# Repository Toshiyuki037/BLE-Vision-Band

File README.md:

<!-- BADGES -->

<br />

<!-- TITLE -->

<div align="center">
  <h1>WBLE Vision Band</h1>
  <p><strong>Embedded BLE Vision System with Haptic Feedback</strong></p>

  <p>
    A wrist-mounted system that performs on-device image recognition and communicates results through real-time haptic feedback.
  </p>

  <br />

<a href="#">🎥 View Demo (Coming Soon)</a>

</div>

---

## 📌 Overview

Vision-Band is a wearable embedded system designed to explore on-device perception in resource-constrained environments.

Motivated by the limitations of the Even Realities G2 Frames—specifically the lack of an integrated camera—this project implements a modular vision pipeline paired with a haptic feedback interface for real-time, non-visual interaction.

---

## 🧠 System Architecture

```bash
[Camera] → [nRF5340 MCU] → [Processing / ML] → [DRV2605L] → [Vibration Motor]
                               ↓
                             [BLE]
```

* SPI camera streams image data to MCU
* MCU performs lightweight processing / inference
* Haptic driver converts results into vibration feedback
* BLE enables debugging + external communication

---

## 🔧 Hardware Components

* NRF5340-DK — main MCU + BLE
* Arducam Mega 5MP SPI Camera — image capture
* DRV2605L — haptic driver
* 3V vibration motor — feedback output
* Li-ion battery (500mAh) — power
* TP4056 — charging module

---

## DOCUMENTATION (BOM)

A dated and recorded log of all my research and development.
👉 https://app.notion.com/p/Vision-Band-3348546487d380519d59cf720e47a7b5

---

## 📦 Bill of Materials (BOM)

A detailed breakdown of all components, costs, and sourcing is available below:

👉 https://docs.google.com/spreadsheets/d/1EQedtdF9KUZCxSDgVT32OZnp6HhoeuN5VWY41QO01Ro/edit?usp=sharing

* Includes part numbers, suppliers, and prototyping cost (~$187)
* Documents full hardware stack for reproducibility

---

## ⚙️ Software Stack

* Embedded firmware (C/C++)
* SPI image acquisition pipeline
* I²C haptic control (DRV2605L)
* BLE communication (Nordic SDK)
* Lightweight image recognition (TinyML / rule-based)

---

## 🚀 Features

* On-device image capture and processing
* Real-time haptic feedback output
* BLE-enabled communication interface
* Fully self-contained wearable prototype
* End-to-end embedded system (hardware + firmware integration)

---

## 📊 Challenges & Engineering Tradeoffs

* **Memory constraints:** Limited RAM for image buffering
* **Bandwidth limits:** SPI camera throughput bottlenecks
* **Power system limitations:** TP4056 lacks load sharing
* **Compute vs latency:** Balancing ML accuracy and responsiveness

---

## 🔋 Power Considerations

* Powered by 3.7V Li-ion battery (500mAh)
* Charging via TP4056
* System currently optimized for prototyping, not all-day wearable use

---

## 🛠️ Getting Started

### Prerequisites

* Arduino IDE or Nordic SDK
* USB connection for NRF5340-DK
* Basic embedded development setup

### Installation

```bash
git clone https://github.com/Toshiyuki037/BLE-Vision-Band.git
```

1. Open firmware in IDE
2. Connect hardware components
3. Flash firmware to board
4. Power via battery + charging module

---

## 📁 Project Structure

```bash
/firmware      → Embedded code  
/hardware      → Schematics / BOM  
/docs          → Design notes  
```

---

## 🗺️ Roadmap

* [x] Hardware integration
* [x] Camera + MCU interface
* [ ] Image recognition optimization
* [ ] Power system redesign
* [ ] Custom PCB
* [ ] Wearable enclosure

---

## 📜 License

Distributed under the MIT License.

---

## 📬 Contact

GitHub: https://github.com/Toshiyuki037

Project Link:
https://github.com/Toshiyuki037/BLE-Vision-Band

---

<p align="center">↑ Back to top</p>

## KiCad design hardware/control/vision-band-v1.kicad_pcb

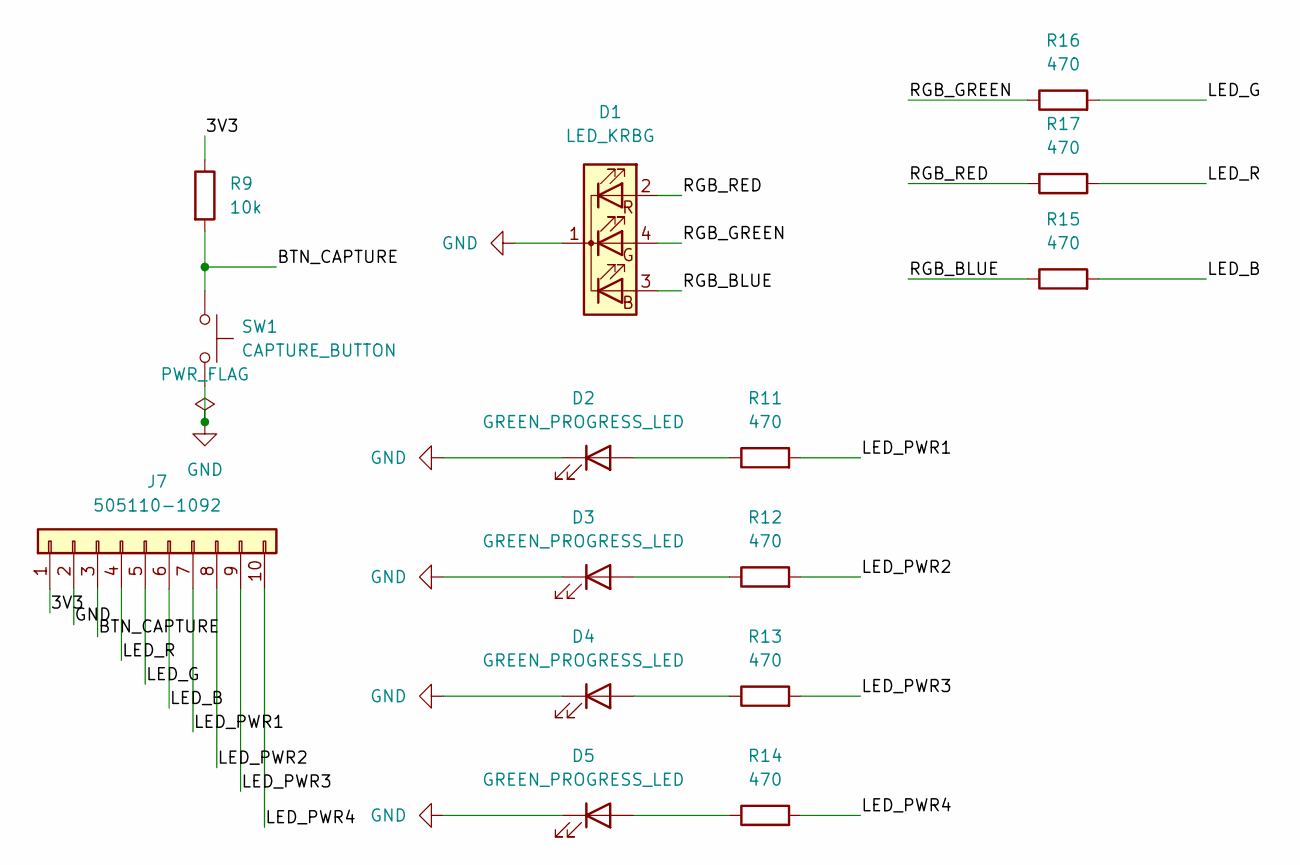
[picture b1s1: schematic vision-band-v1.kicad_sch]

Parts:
D1: LED_KRBG; APTF1616SEJ3ZGGVBDC_KNB; MPN APTF1616LSEKJ3ZGKQBC
D2, D3, D4, D5: GREEN_PROGRESS_LED; LED_0603_1608Metric; MPN APT1608LZGCK
J7: 505110-1092; MOLEX_5051101092; MPN 505110-1092
R9: 10k; R_0603_1608Metric; MPN RC0603FR-0710KL
R11, R12, R13, R14, R15, R16, R17: 470; R_0603_1608Metric; MPN RC0603FR-07470RL
SW1: CAPTURE_BUTTON; SW_SPST_TL3305A; MPN TL3305AF160QG

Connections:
/3V3: J7.1, R9.1
/BTN_CAPTURE: J7.3, R9.2, SW1.1
/LED_B: J7.6, R15.2
/LED_G: J7.5, R16.2
/LED_PWR1: J7.7, R11.2
/LED_PWR2: J7.8, R12.2
/LED_PWR3: J7.9, R13.2
/LED_PWR4: J7.10, R14.2
/LED_R: J7.4, R17.2
/RGB_BLUE: D1.3 (BA), R15.1
/RGB_GREEN: D1.4 (GA), R16.1
/RGB_RED: D1.2 (RA), R17.1
GND: D1.1 (K), D2.1 (K), D3.1 (K), D4.1 (K), D5.1 (K), J7.2, SW1.2
unnamed: D2.2 (A), R11.1
unnamed: D3.2 (A), R12.1
unnamed: D4.2 (A), R13.1
unnamed: D5.2 (A), R14.1

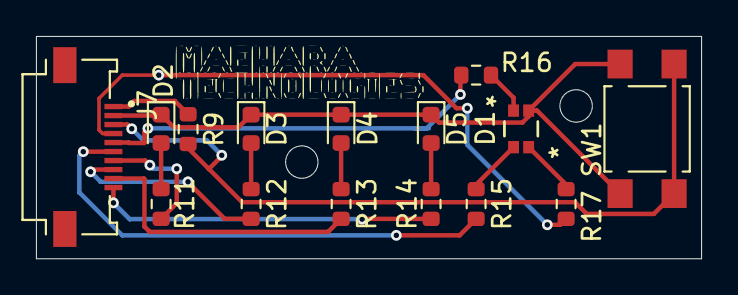
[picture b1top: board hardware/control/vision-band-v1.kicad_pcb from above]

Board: 2 copper layers, 37.0 x 12.3 mm, 15 parts (0 on the bottom side), 17 nets.

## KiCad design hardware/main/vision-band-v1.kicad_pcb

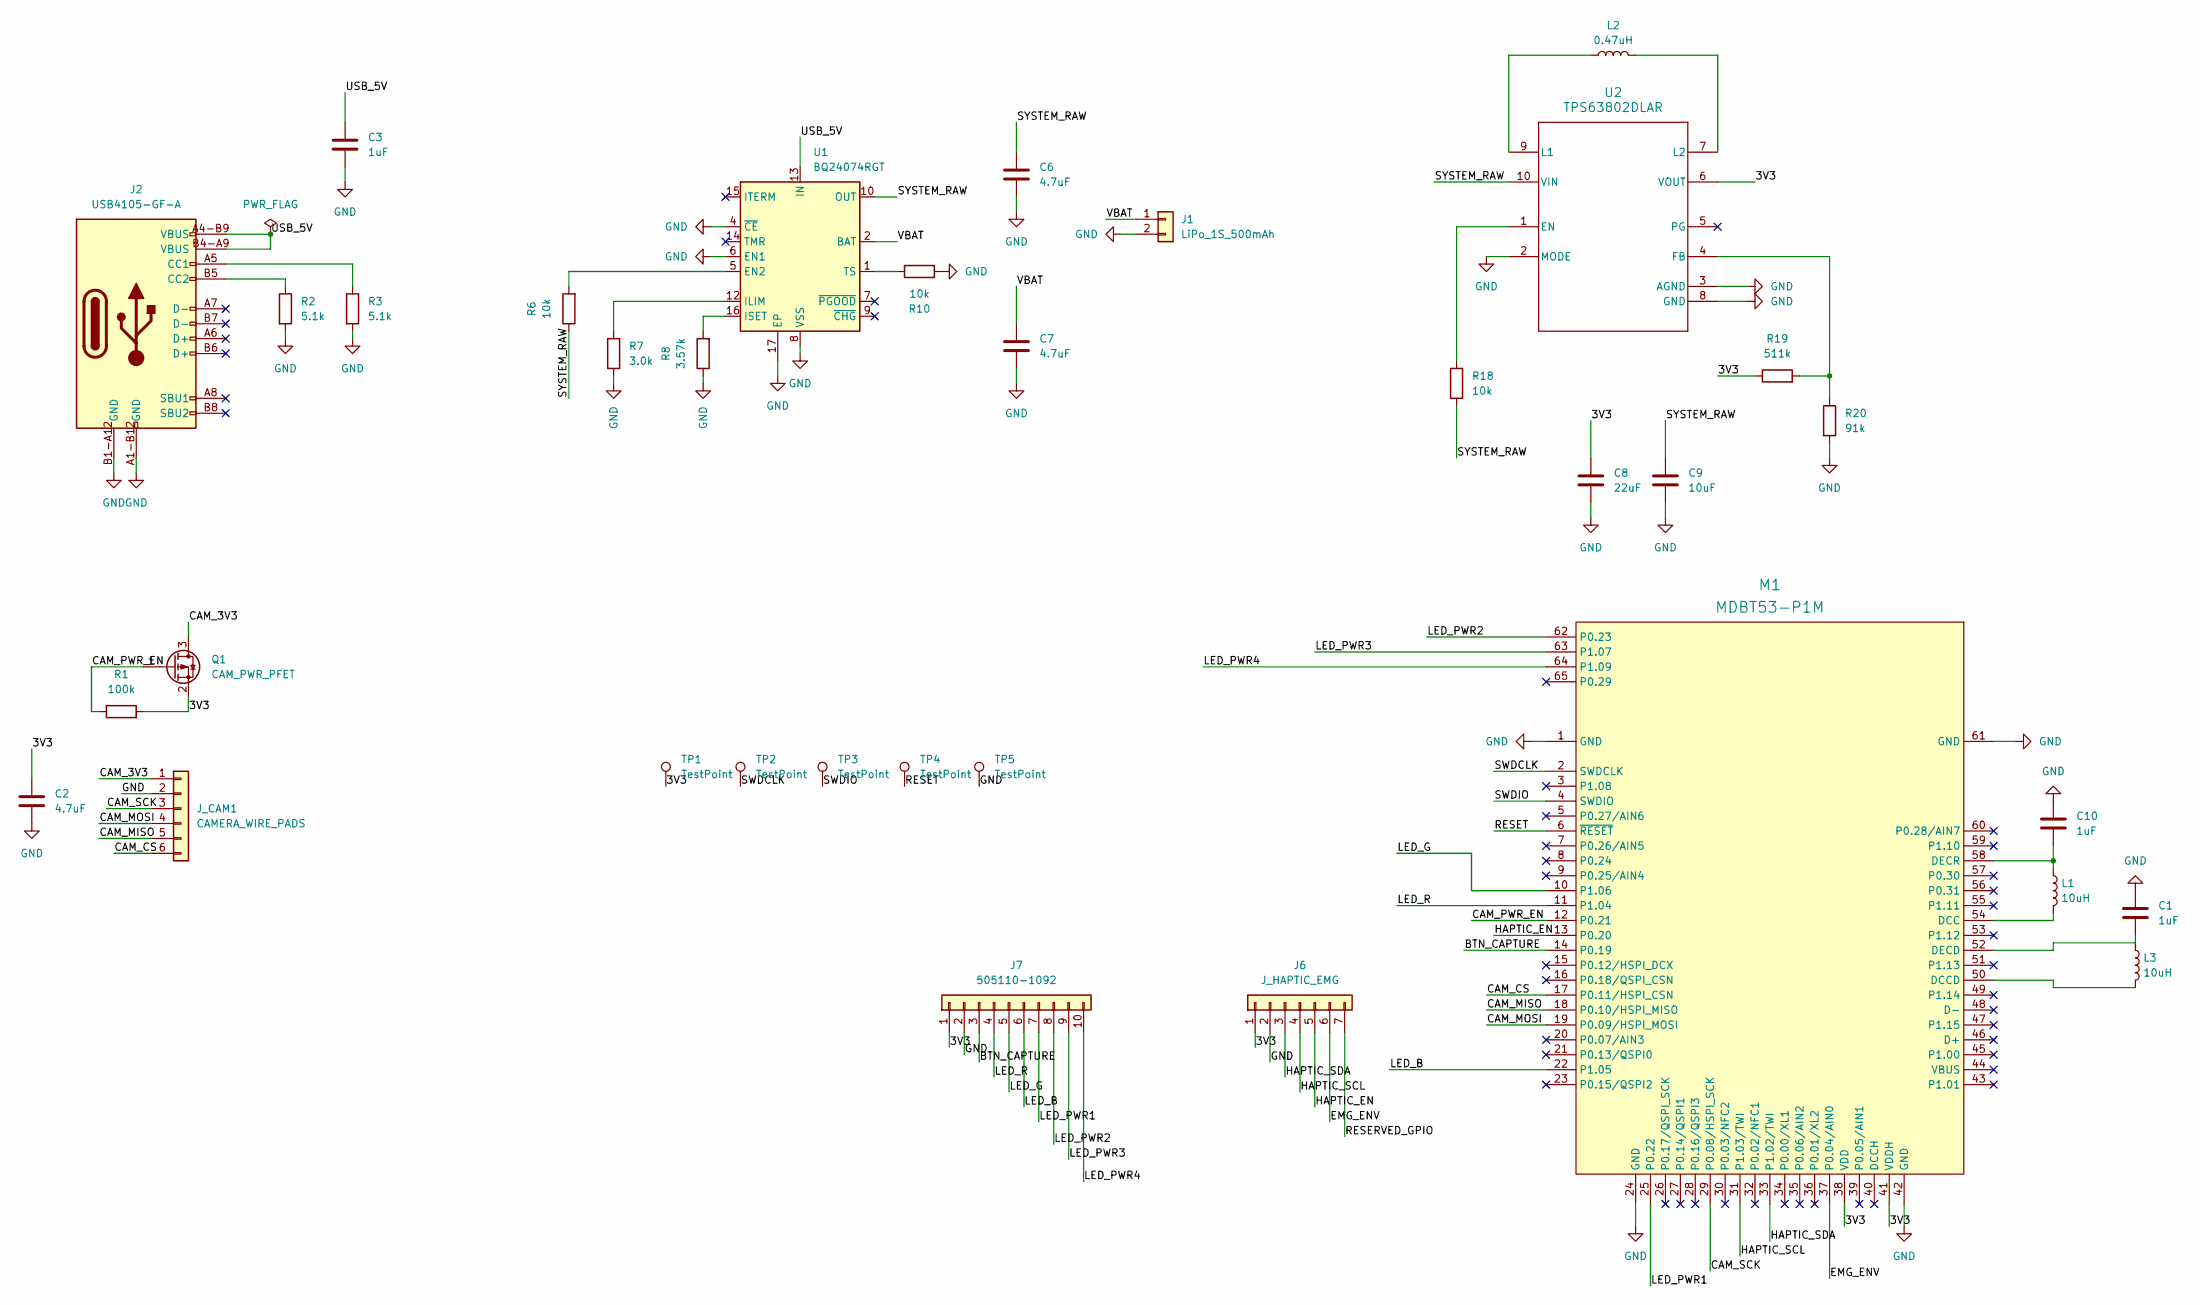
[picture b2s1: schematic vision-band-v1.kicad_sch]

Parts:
C1, C3, C10: 1uF; C_0603_1608Metric; MPN GRM188R71A105KA61J
C2, C6, C7: 4.7uF; C_0603_1608Metric; MPN GRM185R61A475KE11D
C8: 22uF; C_0805_2012Metric; MPN GRM21BR61A226ME51K
C9: 10uF; C_0603_1608Metric; MPN GRM188R61A106ME69D
J1: LiPo_1S_500mAh; JST_PH_S2B-PH-SM4-TB_1x02-1MP_P2.00mm_Horizontal; MPN S2B-PH-SM4-TB(LF)(SN)
J2: USB4105-GF-A; MPN USB4105-GF-A
J6: J_HAPTIC_EMG; TE_0-1734839-7_1x07-1MP_P0.5mm_Horizontal; MPN 0-1734839-7
J7: 505110-1092; MOLEX_5051101092; MPN 505110-1092
J_CAM1: CAMERA_WIRE_PADS; CAMERA_WIRE_PADS_2x3_P2.00mm
L1, L3: 10uH; L_0603_1608Metric; MPN 0603AF-103XJRW
L2: 0.47uH; DFE201612E-R47M; MPN DFE201612E-R47M=P2
M1: MDBT53-P1M; MPN MDBT53-P1M
Q1: CAM_PWR_PFET; SOT-23; MPN DMP2035U-7
R1: 100k; R_0603_1608Metric; MPN RC0603FR-07100KL
R2, R3: 5.1k; R_0603_1608Metric; MPN RC0603FR-075K1L
R6, R10, R18: 10k; R_0603_1608Metric; MPN RC0603FR-0710KL
R7: 3.0k; R_0603_1608Metric; MPN RC0603FR-073KL
R8: 3.57k; R_0603_1608Metric; MPN AC0603FR-073K57L
R19: 511k; R_0603_1608Metric; MPN RC0603FR-07511KL
R20: 91k; R_0603_1608Metric; MPN RC0603FR-0791KL
TP1, TP2, TP3, TP4, TP5: TestPoint; TestPoint_Pad_D1.0mm
U1: BQ24074RGT; BQ24074RGT_VQFN16_EP; MPN BQ24074RGT
U2: TPS63802DLAR; MPN TPS63802DLAR

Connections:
/3V3: C2.1, C8.1, J6.1, J7.1, M1.38 (VDD), M1.41 (VDDH), Q1.2 (S), R1.2, R19.1, TP1.1 (1_1), U2.6 (VOUT)
/BTN_CAPTURE: J7.3, M1.14 (P0.19)
/CAM_3V3: J_CAM1.1, Q1.3 (D)
/CAM_CS: J_CAM1.6, M1.17 (P0.11/HSPI_CSN)
/CAM_MISO: J_CAM1.5, M1.18 (P0.10/HSPI_MISO)
/CAM_MOSI: J_CAM1.4, M1.19 (P0.09/HSPI_MOSI)
/CAM_PWR_EN: M1.12 (P0.21), Q1.1 (G), R1.1
/CAM_SCK: J_CAM1.3, M1.29 (P0.08/HSPI_SCK)
/EMG_ENV: J6.6, M1.37 (P0.04/AIN0)
/HAPTIC_EN: J6.5, M1.13 (P0.20)
/HAPTIC_SCL: J6.4, M1.31 (P1.03/TWI)
/HAPTIC_SDA: J6.3, M1.33 (P1.02/TWI)
/LED_B: J7.6, M1.22 (P1.05)
/LED_G: J7.5, M1.10 (P1.06)
/LED_PWR1: J7.7, M1.25 (P0.22)
/LED_PWR2: J7.8, M1.62 (P0.23)
/LED_PWR3: J7.9, M1.63 (P1.07)
/LED_PWR4: J7.10, M1.64 (P1.09)
/LED_R: J7.4, M1.11 (P1.04)
/RESERVED_GPIO: J6.7
/RESET: M1.6 (~RESET), TP4.1 (1_1)
/SWDCLK: M1.2 (SWDCLK), TP2.1 (1_1)
/SWDIO: M1.4 (SWDIO), TP3.1 (1_1)
/SYSTEM_RAW: C6.1, C9.1, R6.1, R18.1, U1.10 (OUT), U1.11 (OUT), U2.10 (VIN)
/USB_5V: C3.1, J2.A4-B9 (VBUS), J2.B4-A9 (VBUS), U1.13 (IN)
/VBAT: C7.1, J1.1, U1.2 (BAT), U1.3 (BAT)
GND: C1.1, C2.2, C3.2, C6.2, C7.2, C8.2, C9.2, C10.1, J1.2, J2.A1-B12 (GND), J2.B1-A12 (GND), J6.2, J7.2, J_CAM1.2, M1.1 (GND), M1.24 (GND), M1.42 (GND), M1.61 (GND), R2.2, R3.2, R7.1, R8.1, R10.1, R20.2, TP5.1 (1_1), U1.4 (~CE), U1.6 (EN1), U1.8 (VSS), U1.17 (EP), U2.2 (MODE), U2.3 (AGND), U2.8 (GND)
unnamed: J2.A5 (CC1), R3.1
unnamed: J2.B5 (CC2), R2.1
unnamed: L1.2, M1.54 (DCC)
unnamed: L3.2, M1.50 (DCCD)
unnamed: C1.2, L3.1, M1.52 (DECD)
unnamed: C10.2, L1.1, M1.58 (DECR)
unnamed: R6.2, U1.5 (EN2)
unnamed: R7.2, U1.12 (ILIM)
unnamed: R8.2, U1.16 (ISET)
unnamed: R10.2, U1.1 (TS)
unnamed: R18.2, U2.1 (EN)
unnamed: R19.2, R20.1, U2.4 (FB)
unnamed: L2.1, U2.9 (L1)
unnamed: L2.2, U2.7 (L2)

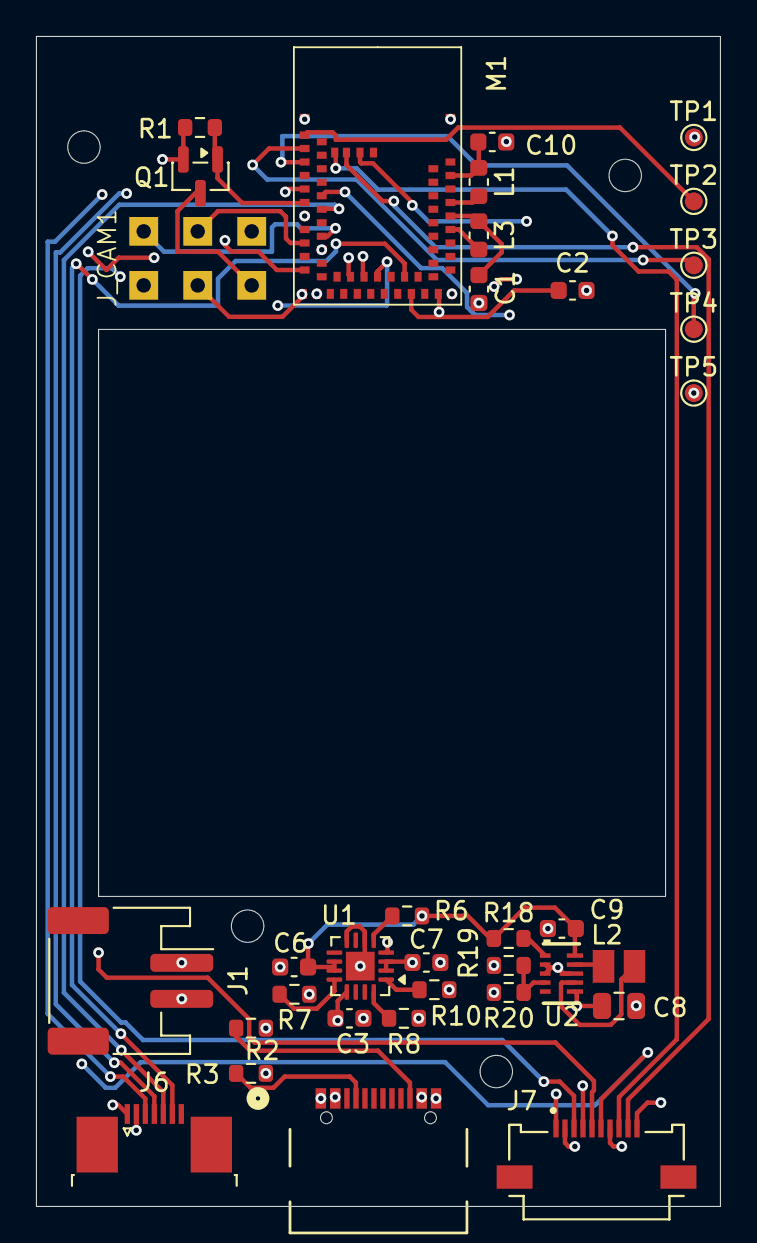
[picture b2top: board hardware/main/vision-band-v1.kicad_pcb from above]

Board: 4 copper layers, 38.0 x 65.0 mm, 35 parts (0 on the bottom side), 40 nets.

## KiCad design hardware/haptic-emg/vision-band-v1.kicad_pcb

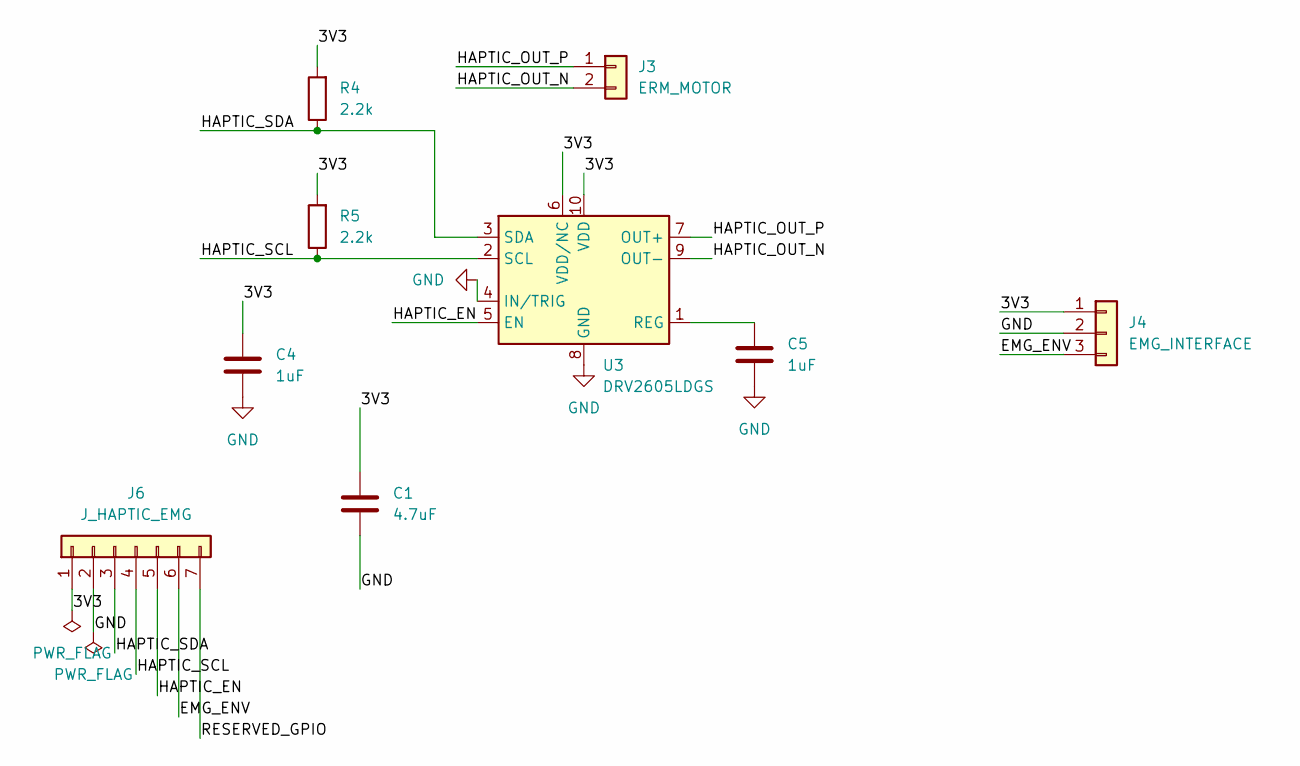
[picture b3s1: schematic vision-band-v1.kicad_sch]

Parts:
C1: 4.7uF; C_0603_1608Metric; MPN GRM185R61A475KE11D
C4, C5: 1uF; C_0603_1608Metric; MPN GRM188R71A105KA61J
J3: ERM_MOTOR; SolderWire-0.5sqmm_1x02_P4.6mm_D0.9mm_OD2.1mm_Relief
J4: EMG_INTERFACE; JST_SH_SM03B-SRSS-TB_1x03-1MP_P1.00mm_Horizontal; MPN SM03B-SRSS-TB(LF)(SN)
J6: J_HAPTIC_EMG; TE_0-1734839-7_1x07-1MP_P0.5mm_Horizontal; MPN 0-1734839-7
R4, R5: 2.2k; R_0603_1608Metric; MPN RC0603FR-072K2L
U3: DRV2605LDGS; TSSOP-10_3x3mm_P0.5mm; MPN DRV2605LDGSR

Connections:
/3V3: C1.1, C4.1, J4.1, J6.1, R4.2, R5.2, U3.6 (VDD/NC), U3.10 (VDD)
/EMG_ENV: J4.3, J6.6
/HAPTIC_EN: J6.5, U3.5 (EN)
/HAPTIC_OUT_N: J3.2, U3.9 (OUT-)
/HAPTIC_OUT_P: J3.1, U3.7 (OUT+)
/HAPTIC_SCL: J6.4, R5.1, U3.2 (SCL)
/HAPTIC_SDA: J6.3, R4.1, U3.3 (SDA)
/RESERVED_GPIO: J6.7
GND: C1.2, C4.2, C5.2, J4.2, J6.2, U3.4 (IN/TRIG), U3.8 (GND)
unnamed: C5.1, U3.1 (REG)

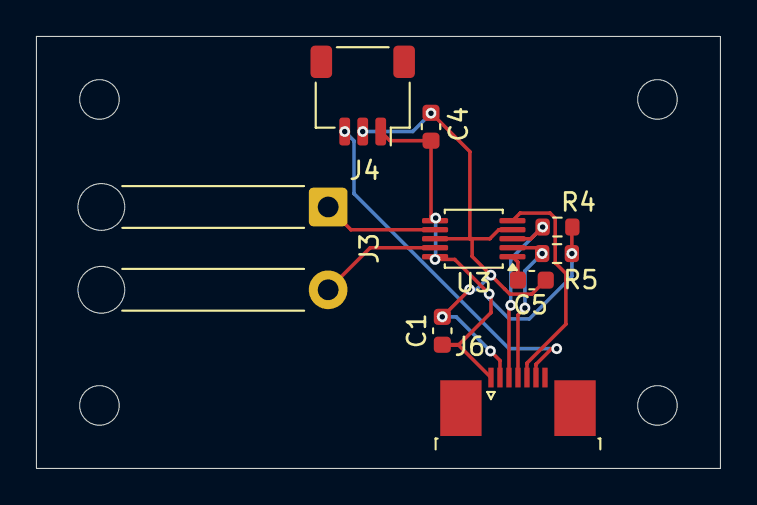
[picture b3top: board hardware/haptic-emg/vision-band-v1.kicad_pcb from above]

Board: 2 copper layers, 38.0 x 24.0 mm, 9 parts (0 on the bottom side), 9 nets.
